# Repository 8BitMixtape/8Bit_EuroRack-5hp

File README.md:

# 8Bit_EuroRack-5hp

This was the first design and concept... 

* single PCB layer as frontplate AND circuit
* screw pots with solded pads on backside, like the 8Bit Mixtape NEO
* Vertical 3.5mm jacks, needs a bit of wiring to the PCB
* Attiny85 Chip on frontside. 8bit style

## Connections
* IN (for programming with audio)
* CV1 and CV2 IN - Connected to the input of potentiometers
* Sync IN - same connection as buttons. read as High to check for Sync signal (still needs to be coded)
* Sync OUT - from reset pin aka PB5 - change fuse settings to disable reset and solder little jumperpads on PCB
* NEO OUT - from PB0 to control NEO-Pixels or use as any other I/O pin.
* Coconut - That's the Main sound output aka PB0 with little RC filter

## Interface design drafts

## KiCAD PCB and 3d View

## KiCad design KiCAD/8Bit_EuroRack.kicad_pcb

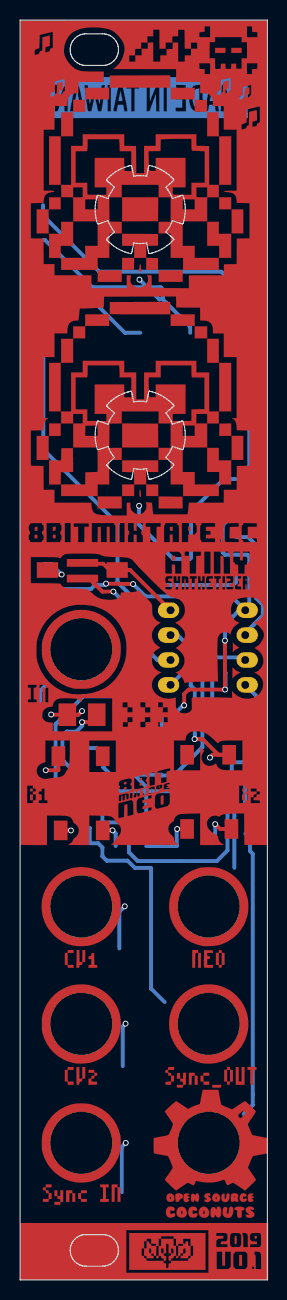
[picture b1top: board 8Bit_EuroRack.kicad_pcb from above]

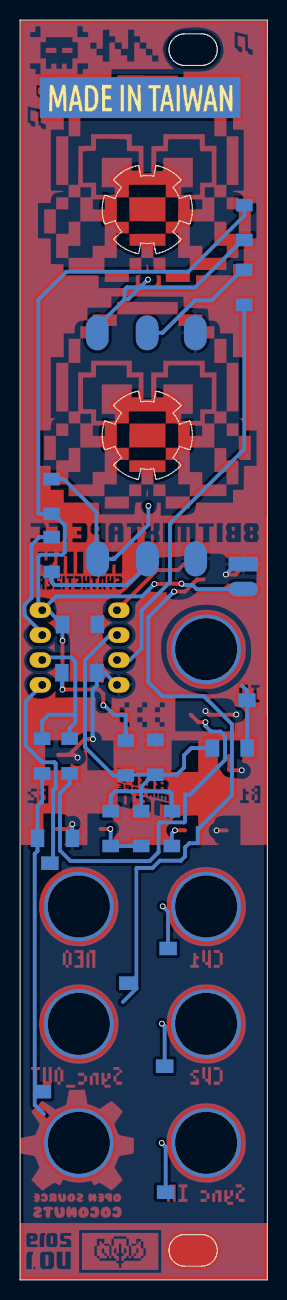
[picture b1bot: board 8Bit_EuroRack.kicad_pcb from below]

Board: 2 copper layers, 25.2 x 128.5 mm, 25 parts (16 on the bottom side), 15 nets.

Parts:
C1, C2, C3: 100nF; C_1206_HandSoldering
C4: 10uF; C_1206_HandSoldering
D-OUT1: LED; LED_2835_minimal
J4: Con_3-5V; Bat_connector_SMD
J6: Sync_Jumper; Sync_jumper
POT1-MAIN1, POT2-CV1: POT 10K lin; Potentiometer_backPads_noHole
R1, R2, R3, R4, R5: 22k; R_1206_HandSoldering
R6, R7: 22K; R_1206_HandSoldering
R8: 330; R_1206_HandSoldering
R10, R11: 4.7K; R_1206_HandSoldering
R13: 1K; R_1206_HandSoldering
Ref**: Val**; 8Bit_EuroRack-NEO_mini_frontplate
SW2, SW3: SW_Push; TACTILE-PTH_6mm_SMD
SW4: SW_Push; SW_SPST_FSMSM
U1: ATTINY85-20SU; Attiny_DIP-8_W7.62mm_mod

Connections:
+3V3: C2.1, C4.1, J4.2, R1.1, R10.1, R11.1, U1.8
But-L: R3.2, SW2.1
But-R: R4.2, R5.2, SW3.1
CV1_IN: POT2-CV1.1, R10.2
CV2_IN: POT1-MAIN1.1, R11.2
CV_OUT: C3.1, R8.1
GND: C2.2, C3.2, C4.2, D-OUT1.1, J4.1, POT1-MAIN1.3, POT2-CV1.3, R2.2, SW2.2, SW3.2, SW4.2, U1.4
unnamed: D-OUT1.2, R13.2
unnamed: J6.1, SW4.1, U1.1
unnamed: POT1-MAIN1.2, R7.2
unnamed: POT2-CV1.2, R6.2
PB1: R8.2, R13.1, U1.6
PB2/A1: R7.1, U1.7
PB4/A2: R6.1, U1.3
Sync_IN: C1.2, R1.2, R2.1, R3.1, R4.1, R5.1, U1.2

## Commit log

2019-05-06 clean files
2019-05-06 adding screenshots
2019-05-15 adding photos
2019-05-15 more photos
